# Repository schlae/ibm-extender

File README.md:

# IBM 5161 Expansion Chassis Cards

This project duplicates both the extender and receiver cards used in the IBM
5161 expansion chassis. This is a box that looks identical to an IBM PC, only
it has simple backplane instead of a motherboard. An extender card located in
a host PC/XT system connects to a receiver card located in the expansion
chassis using a large 62-pin D-sub cable.

Even if you don't own (all or part) of an IBM 5161, this project may still be
useful to you. It works perfectly with various passive ISA backplanes! There
is one slight catch--the 14.318MHz ISA bus clock signal is generated on the
IBM backplane but not typically on passive ISA backplanes. Not all cards need
this signal, however. Often you can check by tracing the edge connector contact
B30 on the back of an ISA card. It is second-furthest from the bracket. If the
contact is missing or not connected to a trace, the card should work.

Further information on the IBM 5161 is available from [minuszerodegrees.net](http://minuszerodegrees.net/5161/doco/5161_documentation.htm).

Someone else has reverse engineered and cloned the 5161 backplane. See [here](https://gitlab.com/trs-eric/5161-planar-backplane-board).

Incidentally, the 62-pin cable is available from Mouser Electronics,
923-PCL-10162-1E. Use the 1 meter cable; anything longer may cause signal
integrity issues.

The card bracket, Mouser Electronics 534-9200-5, has been reported to fit.
I have not personally tried it.

The IBM PC and XT BIOS run some tests on the card on boot. If you see an
"1801" code on boot, it may mean something as simple as an unconnected cable
or an unpowered expansion chassis. It'll pop up for any other error with the
card. For troubleshooting, you may have more luck writing test programs in
BASIC using the inp() and out() functions. Test registers are documented
in the [IBM technical reference manual](http://minuszerodegrees.net/oa/OA%20-%20IBM%20Expansion%20Unit%20(5161).pdf).

On to the cards themselves! These are both 4-layer boards. I got mine with
immersion gold edge fingers and a 30 degree edge bevel, but both these are
optional. The ideal is to use selective hard gold for the edge fingers,
but this tends to be quite expensive.

## Extender Card
Here is what the extender card looks like. Components shown may vary from the
official bill of materials.

There is a switch bank in the upper left corner. This configures the wait-state
generator which is necessary if you need to access RAM or ROM on any other card
in the expansion chassis. Placing RAM expansion cards in the chassis is not
recommended since it slows everything down. The wait-state generator starts at
0xEFFFF and extends downwards to the configured address. ROM at 0xF0000-0xFFFFF
is reserved for system BIOS and never gets an additional wait state.

1=On, 0=Off/Open

| Switches  1234 | Address Range with Wait State |
|:--------------:|-------------------------------|
| 1111           | 0x00000-0xEFFFF               |
| 1110           | 0x10000-0xEFFFF               |
| 1101           | 0x20000-0xEFFFF               |
| 1100           | 0x30000-0xEFFFF               |
| 1011           | 0x40000-0xEFFFF               |
| 1010           | 0x50000-0xEFFFF               |
| 1001           | 0x60000-0xEFFFF               |
| 1000           | 0x70000-0xEFFFF               |
| 0111           | 0x80000-0xEFFFF               |
| 0110           | 0x90000-0xEFFFF               |
| 0101           | 0xA0000-0xEFFFF               |
| 0100           | 0xB0000-0xEFFFF               |
| 0011           | 0xC0000-0xEFFFF               |
| 0010           | 0xD0000-0xEFFFF               |
| 0001           | 0xE0000-0xEFFFF               |
| 0000           | Wait-state generator disabled |

Following are reference materials for your convenience.

[Schematic](https://github.com/schlae/ibm-extender/blob/master/Extender/IBMExtender.pdf)

[Bill of materials](https://github.com/schlae/ibm-extender/blob/master/Extender/IBMExtenderBOM.csv)

[Fab files](https://github.com/schlae/ibm-extender/raw/master/Extender/fab/IBMExtender.zip)

### Mistakes in the IBM Schematic
The IBM schematic has some errors:

1. Pin 2 of U1 was tied to EDACK1#. It should have been tied to ECLK to match the layout.
2. U8 pin 14 goes to RN2 pin 1 (pin number not shown on schematic).
3. Pin 2 of RN2 and pin 9 of RN3 were swapped on the schematic compared to the layout.
4. The board itself has a blue wire from pin 11 of U13 to what appears to be pin 4 of U2 (where the signal comes out to a via below the chip, not the actual pin). This wire has been incorporated in my design so you don't have to worry about it.

## Receiver Card
And here is what the receiver card looks like. Again, components shown may vary
from the official bill of materials.

There is one part on here, the delay line TD1, that may be more difficult to
find. It's a DS1005 or a 14T150 which is not something that Mouser stocks
anymore. You may be able to find one on auction sites, brokers, or you might
want to buy a more modern SMD delay line and wire up an adapter board. As long
as it provides a 150ns delay and supports 5V I/O, it should work.

[Schematic](https://github.com/schlae/ibm-extender/blob/master/Receiver/IBMReceiver.pdf)

[Bill of materials](https://github.com/schlae/ibm-extender/blob/master/Receiver/IBMReceiverBOM.csv)

[Fab files](https://github.com/schlae/ibm-extender/raw/master/Receiver/fab/IBMReceiver.zip)

### Mistakes in the IBM Schematic
Again, the IBM schematic has errors in it.

1. Pin 37 and 39 of J1 (D shell connector) are swapped. EDACK3#, EIOR#.
2. Pin 12 of U11 was tied to pin 3 of U2. It should be tied to pin 2 of U2. Signal ENABLE# was tied to pin 2 of U2. It should be tied to pin 3 of U2.

# License

This work is licensed under a Creative Commons Attribution 4.0 International License. See [https://creativecommons.org/licenses/by/4.0/](https://creativecommons.org/licenses/by/4.0/).

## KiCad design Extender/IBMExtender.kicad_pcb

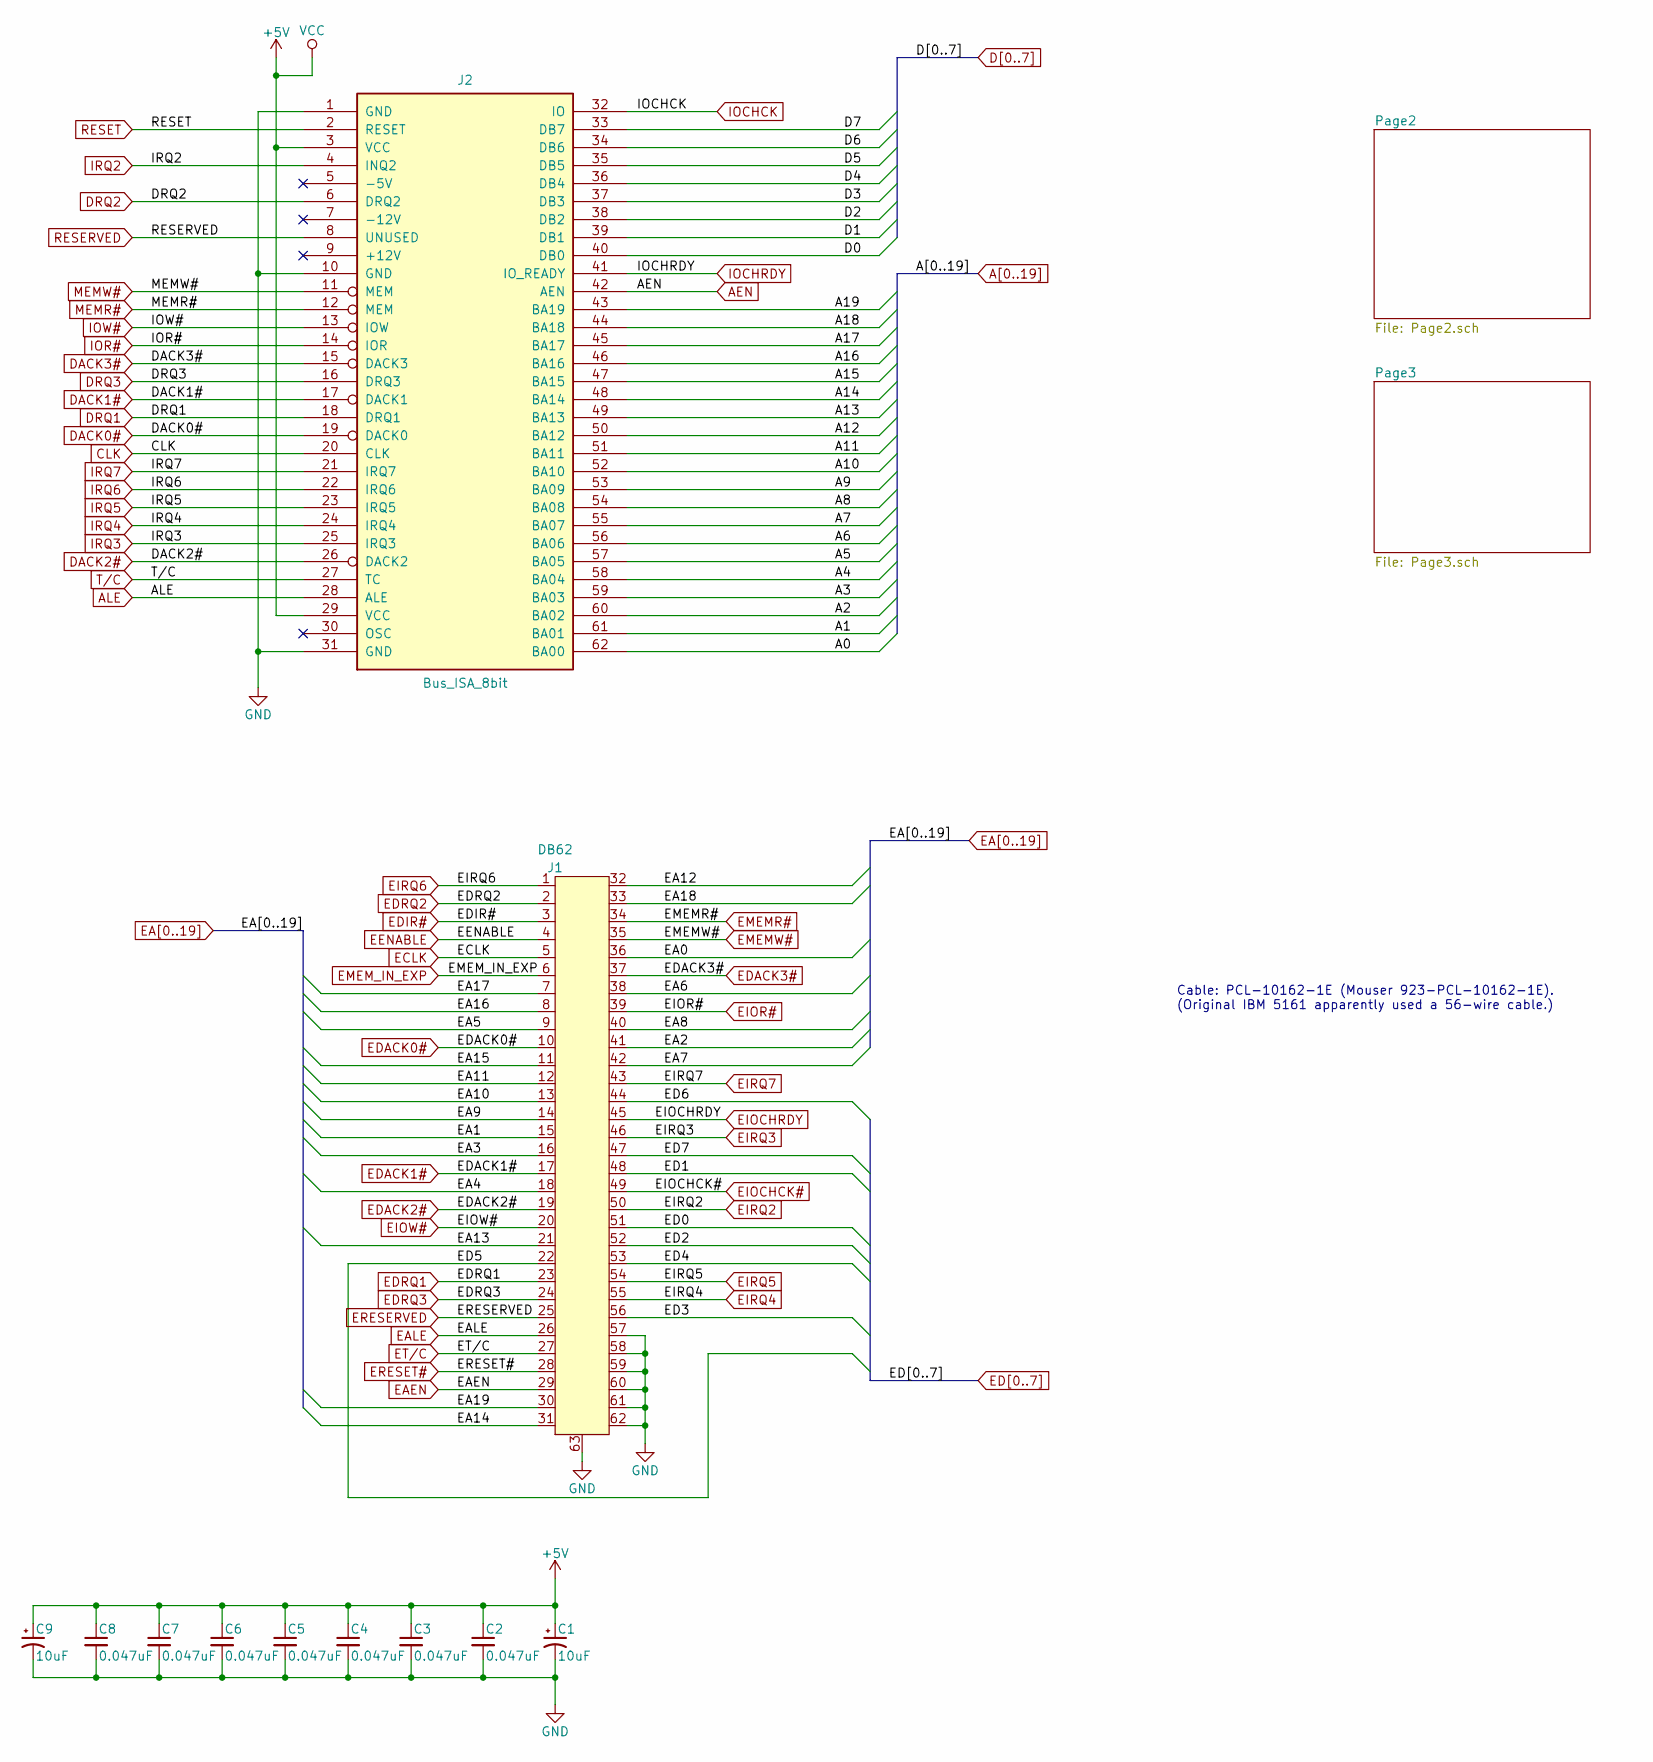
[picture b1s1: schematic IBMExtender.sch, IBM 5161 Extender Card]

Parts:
C1, C9: 10uF; C_Disc_D0.2in_W0.1in_P0.2in
C2, C3, C4, C5, C6, C7, C8: 0.047uF; C_Disc_D0.2in_W0.1in_P0.2in
J1: DB62; Mouser 636-181-062-213R561
J2: Bus_ISA_8bit; BUS_PC

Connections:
+5V: C1.1, C2.1, C3.1, C4.1, C5.1, C6.1, C7.1, C8.1, C9.1, J2.3 (VCC), J2.29 (VCC); also elsewhere on the board
A0: J2.62 (BA00); also elsewhere on the board
A1: J2.61 (BA01); also elsewhere on the board
A2: J2.60 (BA02); also elsewhere on the board
A3: J2.59 (BA03); also elsewhere on the board
A4: J2.58 (BA04); also elsewhere on the board
A5: J2.57 (BA05); also elsewhere on the board
A6: J2.56 (BA06); also elsewhere on the board
A7: J2.55 (BA07); also elsewhere on the board
A8: J2.54 (BA08); also elsewhere on the board
A9: J2.53 (BA09); also elsewhere on the board
A10: J2.52 (BA10); also elsewhere on the board
A11: J2.51 (BA11); also elsewhere on the board
A12: J2.50 (BA12); also elsewhere on the board
A13: J2.49 (BA13); also elsewhere on the board
A14: J2.48 (BA14); also elsewhere on the board
A15: J2.47 (BA15); also elsewhere on the board
A16: J2.46 (BA16); also elsewhere on the board
A17: J2.45 (BA17); also elsewhere on the board
A18: J2.44 (BA18); also elsewhere on the board
A19: J2.43 (BA19); also elsewhere on the board
AEN: J2.42 (AEN); also elsewhere on the board
ALE: J2.28 (ALE); also elsewhere on the board
CLK: J2.20 (CLK); also elsewhere on the board
D0: J2.40 (DB0); also elsewhere on the board
D1: J2.39 (DB1); also elsewhere on the board
D2: J2.38 (DB2); also elsewhere on the board
D3: J2.37 (DB3); also elsewhere on the board
D4: J2.36 (DB4); also elsewhere on the board
D5: J2.35 (DB5); also elsewhere on the board
D6: J2.34 (DB6); also elsewhere on the board
D7: J2.33 (DB7); also elsewhere on the board
DACK0#: J2.19 (DACK0); also elsewhere on the board
DACK1#: J2.17 (DACK1); also elsewhere on the board
DACK2#: J2.26 (DACK2); also elsewhere on the board
DACK3#: J2.15 (DACK3); also elsewhere on the board
DRQ1: J2.18 (DRQ1); also elsewhere on the board
DRQ2: J2.6 (DRQ2); also elsewhere on the board
DRQ3: J2.16 (DRQ3); also elsewhere on the board
EA0: J1.36; also elsewhere on the board
EA1: J1.15; also elsewhere on the board
EA2: J1.41; also elsewhere on the board
EA3: J1.16; also elsewhere on the board
EA4: J1.18; also elsewhere on the board
EA5: J1.9; also elsewhere on the board
EA6: J1.38; also elsewhere on the board
EA7: J1.42; also elsewhere on the board
EA8: J1.40; also elsewhere on the board
EA9: J1.14; also elsewhere on the board
EA10: J1.13; also elsewhere on the board
EA11: J1.12; also elsewhere on the board
EA12: J1.32; also elsewhere on the board
EA13: J1.21; also elsewhere on the board
EA14: J1.31; also elsewhere on the board
EA15: J1.11; also elsewhere on the board
EA16: J1.8; also elsewhere on the board
EA17: J1.7; also elsewhere on the board
EA18: J1.33; also elsewhere on the board
EA19: J1.30; also elsewhere on the board
EAEN: J1.29; also elsewhere on the board
EALE: J1.26; also elsewhere on the board
ECLK: J1.5; also elsewhere on the board
ED0: J1.51; also elsewhere on the board
ED1: J1.48; also elsewhere on the board
ED2: J1.52; also elsewhere on the board
ED3: J1.56; also elsewhere on the board
ED4: J1.53; also elsewhere on the board
ED5: J1.22; also elsewhere on the board
ED6: J1.44; also elsewhere on the board
ED7: J1.47; also elsewhere on the board
EDACK0#: J1.10; also elsewhere on the board
EDACK1#: J1.17; also elsewhere on the board
EDACK2#: J1.19; also elsewhere on the board
EDACK3#: J1.37; also elsewhere on the board
EDIR#: J1.3; also elsewhere on the board
EDRQ1: J1.23; also elsewhere on the board
EDRQ2: J1.2; also elsewhere on the board
EDRQ3: J1.24; also elsewhere on the board
EENABLE: J1.4; also elsewhere on the board
EIOCHCK#: J1.49; also elsewhere on the board
EIOCHRDY: J1.45; also elsewhere on the board
EIOR#: J1.39; also elsewhere on the board
EIOW#: J1.20; also elsewhere on the board
EIRQ2: J1.50; also elsewhere on the board
EIRQ3: J1.46; also elsewhere on the board
EIRQ4: J1.55; also elsewhere on the board
EIRQ5: J1.54; also elsewhere on the board
EIRQ6: J1.1; also elsewhere on the board
EIRQ7: J1.43; also elsewhere on the board
EMEMR#: J1.34; also elsewhere on the board
EMEMW#: J1.35; also elsewhere on the board
EMEM_IN_EXP: J1.6; also elsewhere on the board
ERESERVED: J1.25; also elsewhere on the board
ERESET#: J1.28; also elsewhere on the board
ET/C: J1.27; also elsewhere on the board
GND: C1.2, C2.2, C3.2, C4.2, C5.2, C6.2, C7.2, C8.2, C9.2, J1.57, J1.58, J1.59, J1.60, J1.61, J1.62, J1.63, J2.1 (GND), J2.10 (GND), J2.31 (GND); also elsewhere on the board
IOCHCK: J2.32 (IO); also elsewhere on the board
IOCHRDY: J2.41 (IO_READY); also elsewhere on the board
IOR#: J2.14 (IOR); also elsewhere on the board
IOW#: J2.13 (IOW); also elsewhere on the board
IRQ2: J2.4 (INQ2); also elsewhere on the board
IRQ3: J2.25 (IRQ3); also elsewhere on the board
IRQ4: J2.24 (IRQ4); also elsewhere on the board
IRQ5: J2.23 (IRQ5); also elsewhere on the board
IRQ6: J2.22 (IRQ6); also elsewhere on the board
IRQ7: J2.21 (IRQ7); also elsewhere on the board
MEMR#: J2.12 (MEM); also elsewhere on the board
MEMW#: J2.11 (MEM); also elsewhere on the board
RESERVED: J2.8 (UNUSED); also elsewhere on the board
RESET: J2.2 (RESET); also elsewhere on the board
T/C: J2.27 (TC); also elsewhere on the board

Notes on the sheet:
Cable: PCL-10162-1E (Mouser 923-PCL-10162-1E). (Original IBM 5161 apparently used a 56-wire cable.)

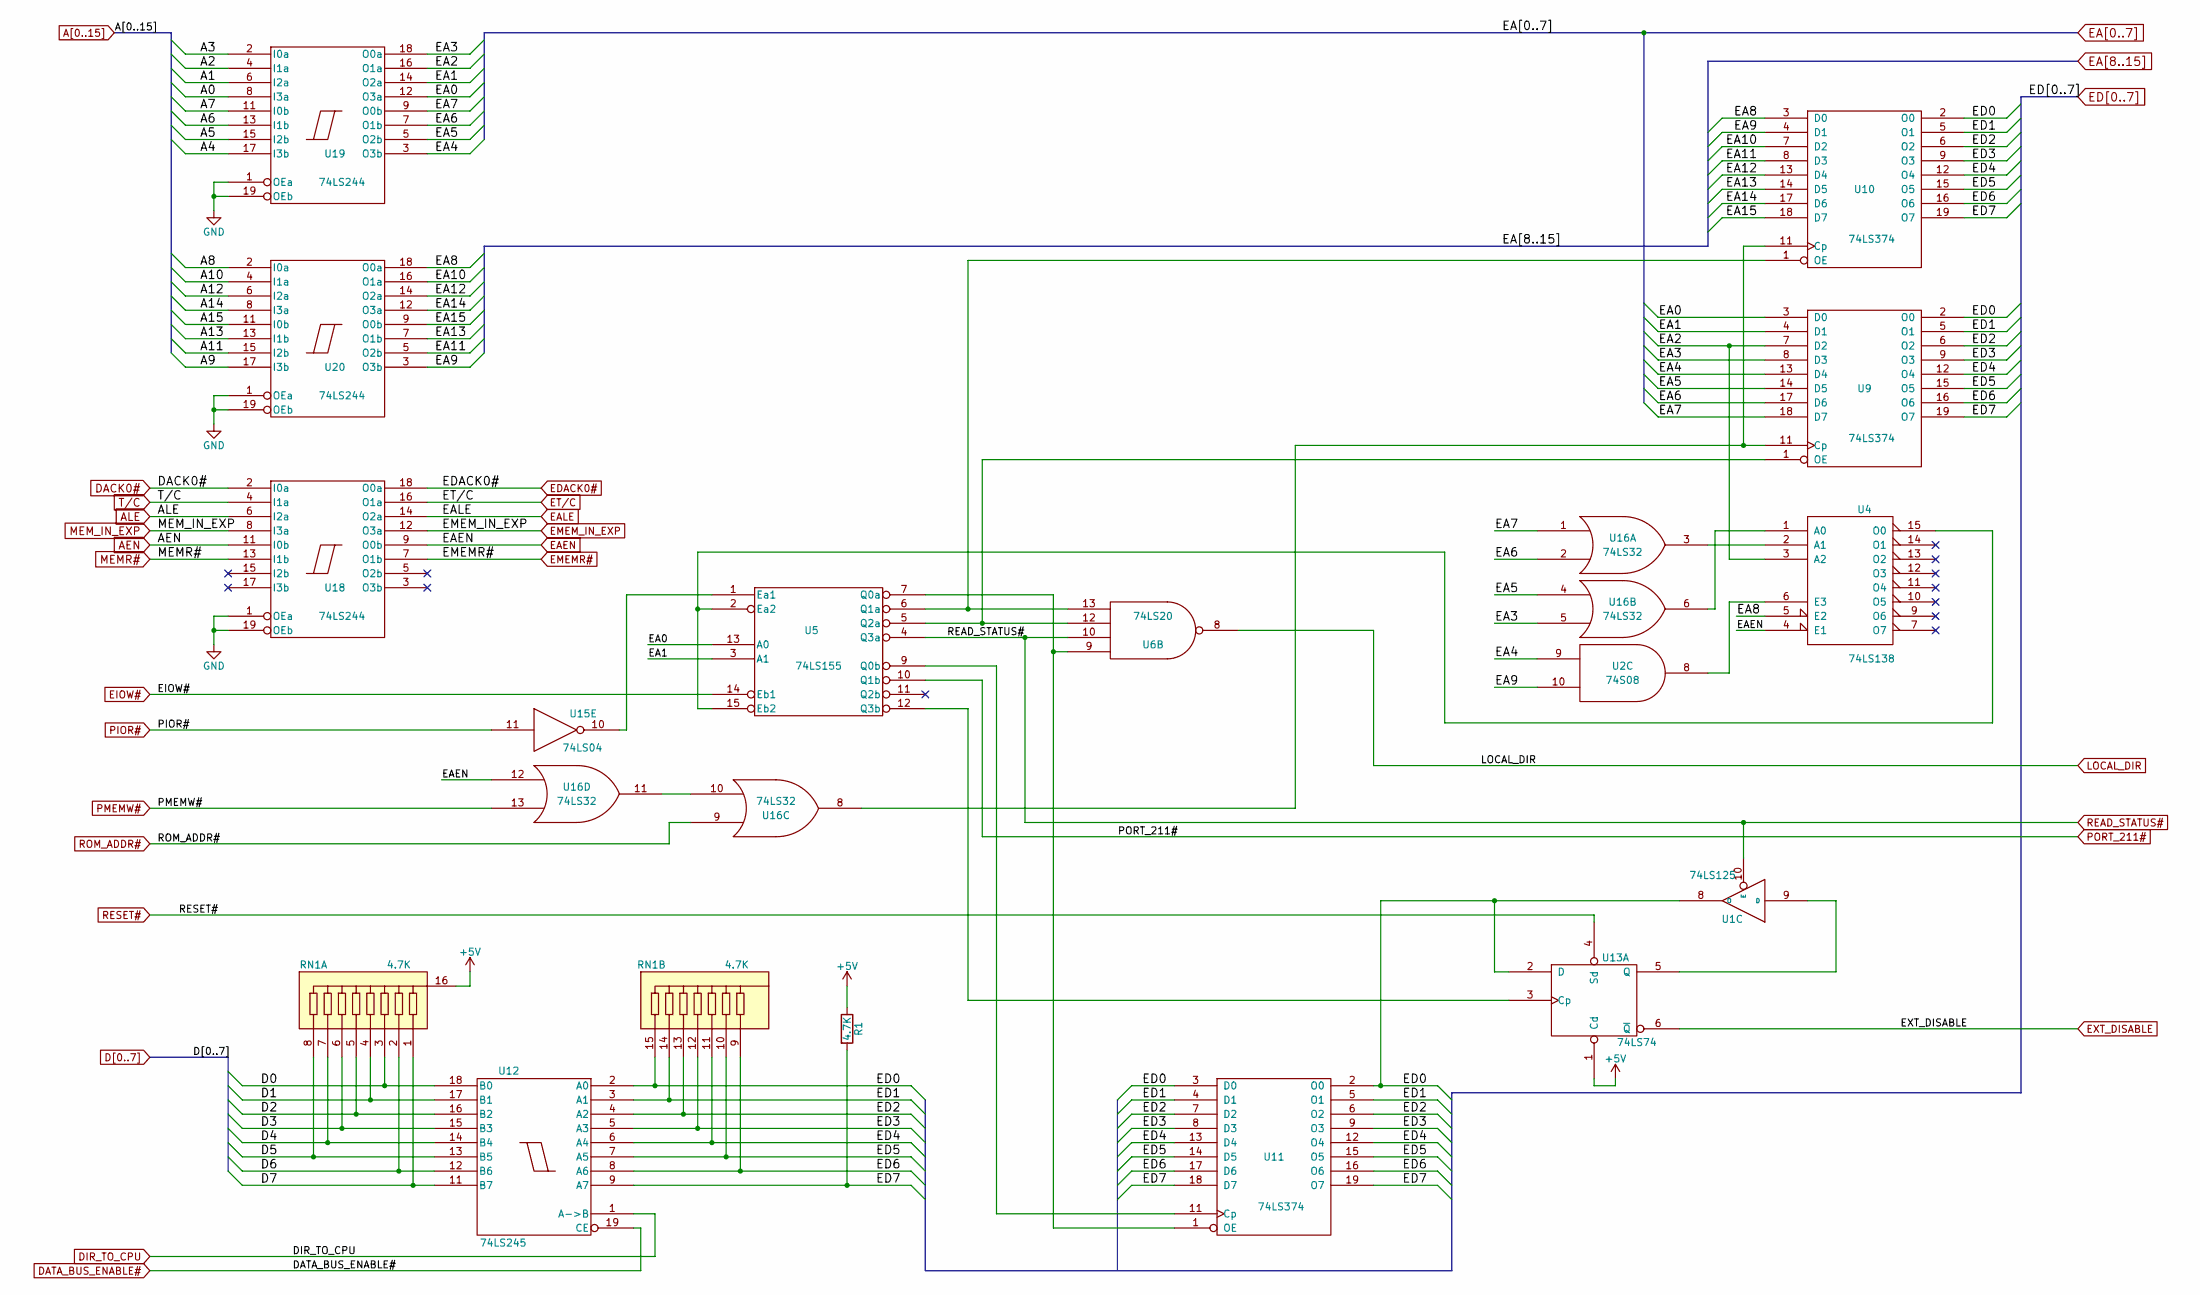
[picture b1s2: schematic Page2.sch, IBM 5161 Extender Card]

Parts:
R1: 4.7K; R_Axial_L0.26in_D0.92in_P0.5in_Horizontal
RN1: 4.7K; DIP254P762X635-16; Mouser 652-4116R-2LF-4.7K
U1: 74LS125; DIP254P762X635-14
U2: 74S08; DIP254P762X635-14
U4: 74LS138; DIP254P762X635-16
U5: 74LS155; DIP254P762X635-16
U6: 74LS20; DIP254P762X635-14
U9, U10, U11: 74LS374; DIP254P762X635-20
U12: 74LS245; DIP254P762X635-20
U13: 74LS74; DIP254P762X635-14
U15: 74LS04; DIP254P762X635-14
U16: 74LS32; DIP254P762X635-14
U18, U19, U20: 74LS244; DIP254P762X635-20

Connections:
+5V: R1.1, RN1.16, U1.14 (VCC), U2.14 (VCC), U4.16 (VCC), U5.16 (VCC), U6.14 (VCC), U9.20 (VCC), U10.20 (VCC), U11.20 (VCC), U12.20 (VCC), U13.1 (Cd), U13.14 (VCC), U15.14 (VCC), U16.14 (VCC), U18.20 (VCC), U19.20 (VCC), U20.20 (VCC); also elsewhere on the board
A0: U19.8 (I3a); also elsewhere on the board
A1: U19.6 (I2a); also elsewhere on the board
A2: U19.4 (I1a); also elsewhere on the board
A3: U19.2 (I0a); also elsewhere on the board
A4: U19.17 (I3b); also elsewhere on the board
A5: U19.15 (I2b); also elsewhere on the board
A6: U19.13 (I1b); also elsewhere on the board
A7: U19.11 (I0b); also elsewhere on the board
A8: U20.2 (I0a); also elsewhere on the board
A9: U20.17 (I3b); also elsewhere on the board
A10: U20.4 (I1a); also elsewhere on the board
A11: U20.15 (I2b); also elsewhere on the board
A12: U20.6 (I2a); also elsewhere on the board
A13: U20.13 (I1b); also elsewhere on the board
A14: U20.8 (I3a); also elsewhere on the board
A15: U20.11 (I0b); also elsewhere on the board
AEN: U18.11 (I0b); also elsewhere on the board
ALE: U18.6 (I2a); also elsewhere on the board
D0: RN1.3, U12.18 (B0); also elsewhere on the board
D1: RN1.4, U12.17 (B1); also elsewhere on the board
D2: RN1.5, U12.16 (B2); also elsewhere on the board
D3: RN1.6, U12.15 (B3); also elsewhere on the board
D4: RN1.7, U12.14 (B4); also elsewhere on the board
D5: RN1.8, U12.13 (B5); also elsewhere on the board
D6: RN1.2, U12.12 (B6); also elsewhere on the board
D7: RN1.1, U12.11 (B7); also elsewhere on the board
DACK0#: U18.2 (I0a); also elsewhere on the board
DATA_BUS_ENABLE#: U12.19 (CE); also elsewhere on the board
DIR_TO_CPU: U12.1 (A->B); also elsewhere on the board
EA0: U5.13 (A0), U9.3 (D0), U19.12 (O3a); also elsewhere on the board
EA1: U5.3 (A1), U9.4 (D1), U19.14 (O2a); also elsewhere on the board
EA2: U4.3 (A2), U9.7 (D2), U19.16 (O1a); also elsewhere on the board
EA3: U9.8 (D3), U16.5, U19.18 (O0a); also elsewhere on the board
EA4: U2.9, U9.13 (D4), U19.3 (O3b); also elsewhere on the board
EA5: U9.14 (D5), U16.4, U19.5 (O2b); also elsewhere on the board
EA6: U9.17 (D6), U16.2, U19.7 (O1b); also elsewhere on the board
EA7: U9.18 (D7), U16.1, U19.9 (O0b); also elsewhere on the board
EA8: U4.5 (E2), U10.3 (D0), U20.18 (O0a); also elsewhere on the board
EA9: U2.10, U10.4 (D1), U20.3 (O3b); also elsewhere on the board
EA10: U10.7 (D2), U20.16 (O1a); also elsewhere on the board
EA11: U10.8 (D3), U20.5 (O2b); also elsewhere on the board
EA12: U10.13 (D4), U20.14 (O2a); also elsewhere on the board
EA13: U10.14 (D5), U20.7 (O1b); also elsewhere on the board
EA14: U10.17 (D6), U20.12 (O3a); also elsewhere on the board
EA15: U10.18 (D7), U20.9 (O0b); also elsewhere on the board
EAEN: U4.4 (E1), U16.12, U18.9 (O0b); also elsewhere on the board
EALE: U18.14 (O2a); also elsewhere on the board
ED0: RN1.15, U1.8 (O), U9.2 (O0), U10.2 (O0), U11.2 (O0), U11.3 (D0), U12.2 (A0), U13.2 (D); also elsewhere on the board
ED1: RN1.14, U9.5 (O1), U10.5 (O1), U11.4 (D1), U11.5 (O1), U12.3 (A1); also elsewhere on the board
ED2: RN1.13, U9.6 (O2), U10.6 (O2), U11.6 (O2), U11.7 (D2), U12.4 (A2); also elsewhere on the board
ED3: RN1.12, U9.9 (O3), U10.9 (O3), U11.8 (D3), U11.9 (O3), U12.5 (A3); also elsewhere on the board
ED4: RN1.11, U9.12 (O4), U10.12 (O4), U11.12 (O4), U11.13 (D4), U12.6 (A4); also elsewhere on the board
ED5: RN1.10, U9.15 (O5), U10.15 (O5), U11.14 (D5), U11.15 (O5), U12.7 (A5); also elsewhere on the board
ED6: RN1.9, U9.16 (O6), U10.16 (O6), U11.16 (O6), U11.17 (D6), U12.8 (A6); also elsewhere on the board
ED7: R1.2, U9.19 (O7), U10.19 (O7), U11.18 (D7), U11.19 (O7), U12.9 (A7); also elsewhere on the board
EDACK0#: U18.18 (O0a); also elsewhere on the board
EIOW#: U5.14 (Eb1); also elsewhere on the board
EMEMR#: U18.7 (O1b); also elsewhere on the board
EMEM_IN_EXP: U18.12 (O3a); also elsewhere on the board
ET/C: U18.16 (O1a); also elsewhere on the board
EXT_DISABLE: U13.6 (~Q); also elsewhere on the board
GND: U1.7 (GND), U2.7 (GND), U4.8 (GND), U5.8 (GND), U6.7 (GND), U9.10 (GND), U10.10 (GND), U11.10 (GND), U12.10 (GND), U13.7 (GND), U15.7 (GND), U16.7 (GND), U18.1 (OEa), U18.10 (GND), U18.19 (OEb), U19.1 (OEa), U19.10 (GND), U19.19 (OEb), U20.1 (OEa), U20.10 (GND), U20.19 (OEb); also elsewhere on the board
LOCAL_DIR: U6.8; also elsewhere on the board
MEMR#: U18.13 (I1b); also elsewhere on the board
MEM_IN_EXP: U18.8 (I3a); also elsewhere on the board
unnamed: U1.9 (D), U13.5 (Q)
unnamed: U2.8, U4.6 (E3)
unnamed: U4.15 (O0), U5.2 (Ea2), U5.15 (Eb2)
unnamed: U5.5 (Q2a), U6.12, U9.1 (OE)
unnamed: U5.6 (Q1a), U6.13, U10.1 (OE)
unnamed: U9.11 (Cp), U10.11 (Cp), U16.8
unnamed: U5.7 (Q0a), U6.9, U11.1 (OE)
unnamed: U5.9 (Q0b), U11.11 (Cp)
unnamed: U5.12 (Q3b), U13.3 (Cp)
unnamed: U5.1 (Ea1), U15.10
unnamed: U4.2 (A1), U16.3
unnamed: U4.1 (A0), U16.6
unnamed: U16.10, U16.11
PIOR#: U15.11; also elsewhere on the board
PMEMW#: U16.13; also elsewhere on the board
PORT_211#: U5.10 (Q1b); also elsewhere on the board
READ_STATUS#: U1.10 (E), U5.4 (Q3a), U6.10; also elsewhere on the board
RESET#: U13.4 (Sd); also elsewhere on the board
ROM_ADDR#: U16.9; also elsewhere on the board
T/C: U18.4 (I1a); also elsewhere on the board

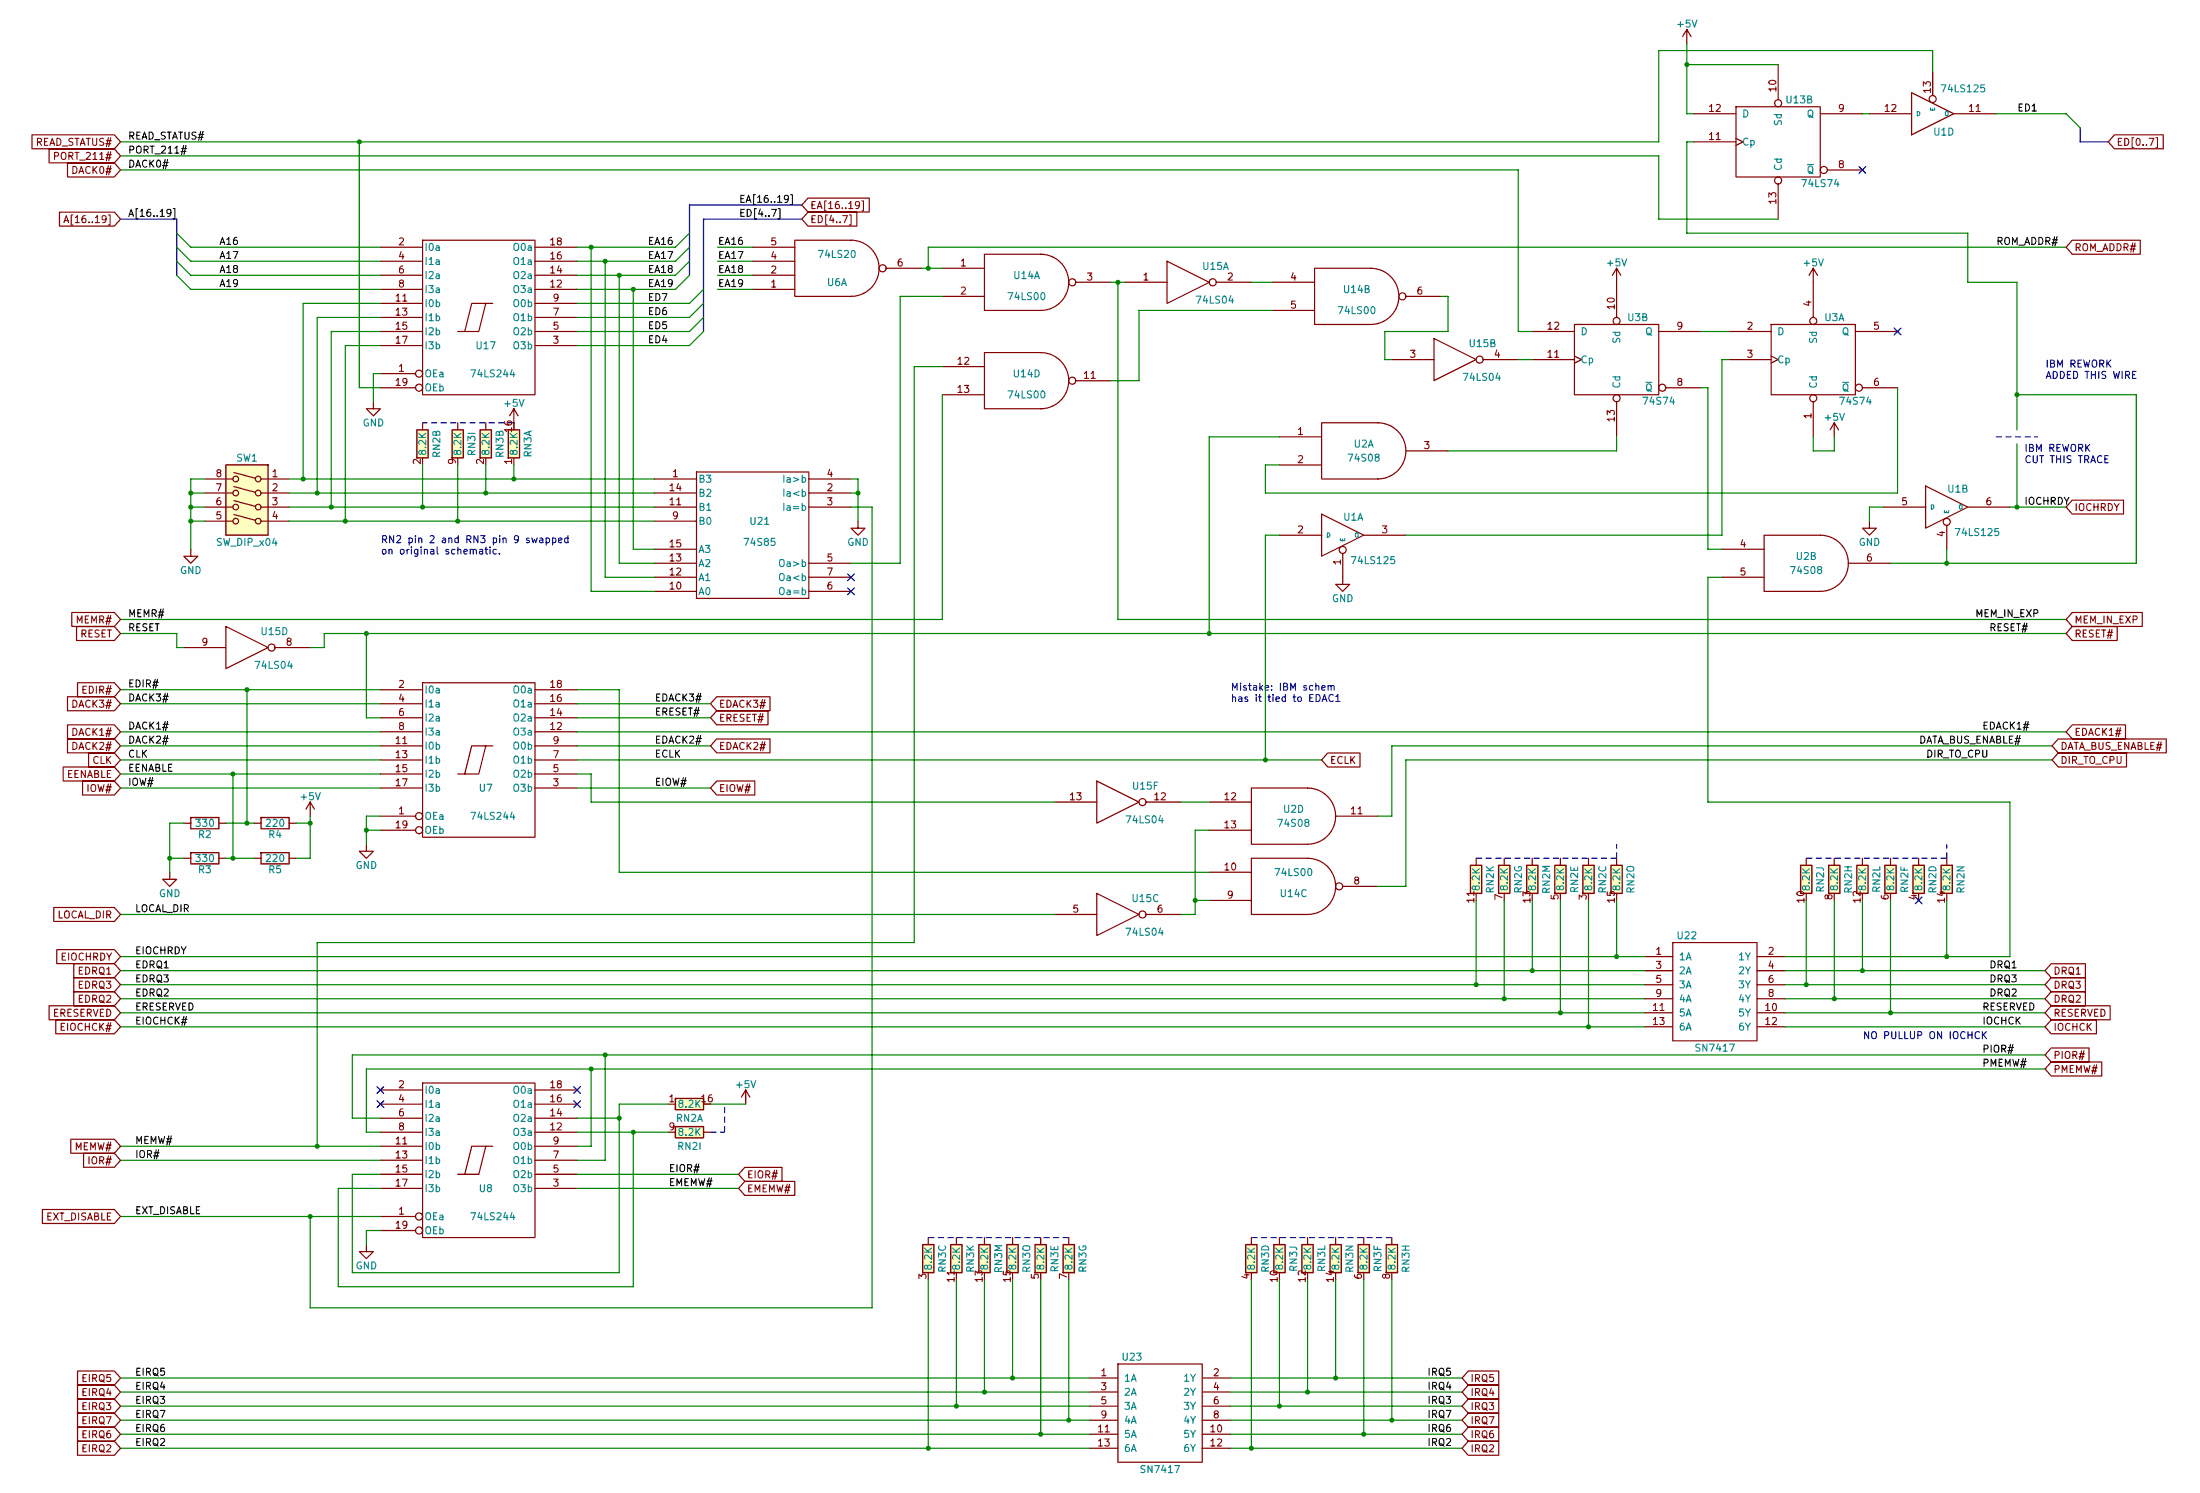
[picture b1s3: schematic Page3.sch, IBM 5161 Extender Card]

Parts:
R2, R3: 330; R_Axial_L0.26in_D0.92in_P0.5in_Horizontal
R4, R5: 220; R_Axial_L0.26in_D0.92in_P0.5in_Horizontal
RN2, RN3: 8.2K; DIP254P762X635-16; Mouser 4116R-2-104LF
SW1: SW_DIP_x04; SW_DIP_x4_W7.62mm_Slide
U1: 74LS125; DIP254P762X635-14
U2: 74S08; DIP254P762X635-14
U3: 74S74; DIP254P762X635-14
U6: 74LS20; DIP254P762X635-14
U7, U8, U17: 74LS244; DIP254P762X635-20
U13: 74LS74; DIP254P762X635-14
U14: 74LS00; DIP254P762X635-14
U15: 74LS04; DIP254P762X635-14
U21: 74S85; DIP254P762X635-16
U22, U23: SN7417; DIP254P762X635-14

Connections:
+5V: R4.1, R5.1, RN2.16, RN3.16, U1.14 (VCC), U2.14 (VCC), U3.1 (Cd), U3.4 (Sd), U3.10 (Sd), U3.14 (VCC), U6.14 (VCC), U7.20 (VCC), U8.20 (VCC), U13.10 (Sd), U13.12 (D), U13.14 (VCC), U14.14 (VCC), U15.14 (VCC), U17.20 (VCC), U21.16 (VCC), U22.14 (VCC), U23.14 (VCC); also elsewhere on the board
A16: U17.2 (I0a); also elsewhere on the board
A17: U17.4 (I1a); also elsewhere on the board
A18: U17.6 (I2a); also elsewhere on the board
A19: U17.8 (I3a); also elsewhere on the board
CLK: U7.13 (I1b); also elsewhere on the board
DACK0#: U3.12 (D); also elsewhere on the board
DACK1#: U7.8 (I3a); also elsewhere on the board
DACK2#: U7.11 (I0b); also elsewhere on the board
DACK3#: U7.4 (I1a); also elsewhere on the board
DATA_BUS_ENABLE#: U2.11; also elsewhere on the board
DIR_TO_CPU: U14.8; also elsewhere on the board
DRQ1: RN2.12, U22.4 (2Y); also elsewhere on the board
DRQ2: RN2.8, U22.8 (4Y); also elsewhere on the board
DRQ3: RN2.10, U22.6 (3Y); also elsewhere on the board
EA16: U6.5, U17.18 (O0a), U21.10 (A0); also elsewhere on the board
EA17: U6.4, U17.16 (O1a), U21.12 (A1); also elsewhere on the board
EA18: U6.2, U17.14 (O2a), U21.13 (A2); also elsewhere on the board
EA19: U6.1, U17.12 (O3a), U21.15 (A3); also elsewhere on the board
ECLK: U1.2 (D), U7.7 (O1b); also elsewhere on the board
ED1: U1.11 (O); also elsewhere on the board
ED4: U17.3 (O3b); also elsewhere on the board
ED5: U17.5 (O2b); also elsewhere on the board
ED6: U17.7 (O1b); also elsewhere on the board
ED7: U17.9 (O0b); also elsewhere on the board
EDACK1#: U7.12 (O3a); also elsewhere on the board
EDACK2#: U7.9 (O0b); also elsewhere on the board
EDACK3#: U7.16 (O1a); also elsewhere on the board
EDIR#: R2.1, R4.2, U7.2 (I0a); also elsewhere on the board
EDRQ1: RN2.13, U22.3 (2A); also elsewhere on the board
EDRQ2: RN2.7, U22.9 (4A); also elsewhere on the board
EDRQ3: RN2.11, U22.5 (3A); also elsewhere on the board
EENABLE: R3.1, R5.2, U7.15 (I2b); also elsewhere on the board
EIOCHCK#: RN2.3, U22.13 (6A); also elsewhere on the board
EIOCHRDY: RN2.15, U22.1 (1A); also elsewhere on the board
EIOR#: U8.5 (O2b); also elsewhere on the board
EIOW#: U7.3 (O3b); also elsewhere on the board
EIRQ2: RN3.3, U23.13 (6A); also elsewhere on the board
EIRQ3: RN3.11, U23.5 (3A); also elsewhere on the board
EIRQ4: RN3.13, U23.3 (2A); also elsewhere on the board
EIRQ5: RN3.15, U23.1 (1A); also elsewhere on the board
EIRQ6: RN3.5, U23.11 (5A); also elsewhere on the board
EIRQ7: RN3.7, U23.9 (4A); also elsewhere on the board
EMEMW#: U8.3 (O3b); also elsewhere on the board
ERESERVED: RN2.5, U22.11 (5A); also elsewhere on the board
ERESET#: U7.14 (O2a); also elsewhere on the board
EXT_DISABLE: U8.1 (OEa), U21.3 (Ia=b); also elsewhere on the board
GND: R2.2, R3.2, SW1.5, SW1.6, SW1.7, SW1.8, U1.1 (E), U1.5 (D), U1.7 (GND), U2.7 (GND), U3.7 (GND), U6.7 (GND), U7.1 (OEa), U7.10 (GND), U7.19 (OEb), U8.10 (GND), U8.19 (OEb), U13.7 (GND), U14.7 (GND), U15.7 (GND), U17.1 (OEa), U17.10 (GND), U21.2 (Ia<b), U21.4 (Ia>b), U21.8 (GND), U22.7 (GND), U23.7 (GND); also elsewhere on the board
IOCHCK: U22.12 (6Y); also elsewhere on the board
IOCHRDY: U1.6 (O); also elsewhere on the board
IOR#: U8.13 (I1b); also elsewhere on the board
IOW#: U7.17 (I3b); also elsewhere on the board
IRQ2: RN3.4, U23.12 (6Y); also elsewhere on the board
IRQ3: RN3.10, U23.6 (3Y); also elsewhere on the board
IRQ4: RN3.12, U23.4 (2Y); also elsewhere on the board
IRQ5: RN3.14, U23.2 (1Y); also elsewhere on the board
IRQ6: RN3.6, U23.10 (5Y); also elsewhere on the board
IRQ7: RN3.8, U23.8 (4Y); also elsewhere on the board
LOCAL_DIR: U15.5; also elsewhere on the board
MEMR#: U14.13; also elsewhere on the board
MEMW#: U8.11 (I0b), U14.12; also elsewhere on the board
MEM_IN_EXP: U14.3, U15.1; also elsewhere on the board
unnamed: RN2.1, U8.14 (O2a), U8.15 (I2b)
unnamed: RN2.2, SW1.3, U17.15 (I2b), U21.11 (B1)
unnamed: RN2.9, U8.12 (O3a), U8.17 (I3b)
unnamed: RN2.14, U2.5, U22.2 (1Y)
unnamed: RN3.1, SW1.1, U17.11 (I0b), U21.1 (B3)
unnamed: RN3.2, SW1.2, U17.13 (I1b), U21.14 (B2)
unnamed: RN3.9, SW1.4, U17.17 (I3b), U21.9 (B0)
unnamed: U1.3 (O), U3.3 (Cp)
unnamed: U1.4 (E), U2.6, U13.11 (Cp)
unnamed: U1.12 (D), U13.9 (Q)
unnamed: U2.2, U3.6 (~Q)
unnamed: U2.3, U3.13 (Cd)
unnamed: U2.4, U3.8 (~Q)
unnamed: U3.2 (D), U3.9 (Q)
unnamed: U14.2, U21.5 (Oa>b)
unnamed: U14.4, U15.2
unnamed: U14.6, U15.3
unnamed: U2.13, U14.9, U15.6
unnamed: U7.18 (O0a), U14.10
unnamed: U14.5, U14.11
unnamed: U3.11 (Cp), U15.4
unnamed: U2.12, U15.12
unnamed: U7.5 (O2b), U15.13
PIOR#: U8.6 (I2a), U8.7 (O1b); also elsewhere on the board
PMEMW#: U8.8 (I3a), U8.9 (O0b); also elsewhere on the board
PORT_211#: U13.13 (Cd); also elsewhere on the board
READ_STATUS#: U1.13 (E), U17.19 (OEb); also elsewhere on the board
RESERVED: RN2.6, U22.10 (5Y); also elsewhere on the board
RESET: U15.9; also elsewhere on the board
RESET#: U2.1, U7.6 (I2a), U15.8; also elsewhere on the board
ROM_ADDR#: U6.6, U14.1; also elsewhere on the board

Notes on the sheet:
NO PULLUP ON IOCHCK
Mistake: IBM schem has it tied to EDAC1
RN2 pin 2 and RN3 pin 9 swapped on original schematic.
IBM REWORK CUT THIS TRACE
IBM REWORK ADDED THIS WIRE

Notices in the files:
Extender/IBMExtender.sch:
Copyright (C) 2018 Eric Schlaepfer
Receiver/IBMReceiver.sch:
Copyright (C) 2017 Eric Schlaepfer
